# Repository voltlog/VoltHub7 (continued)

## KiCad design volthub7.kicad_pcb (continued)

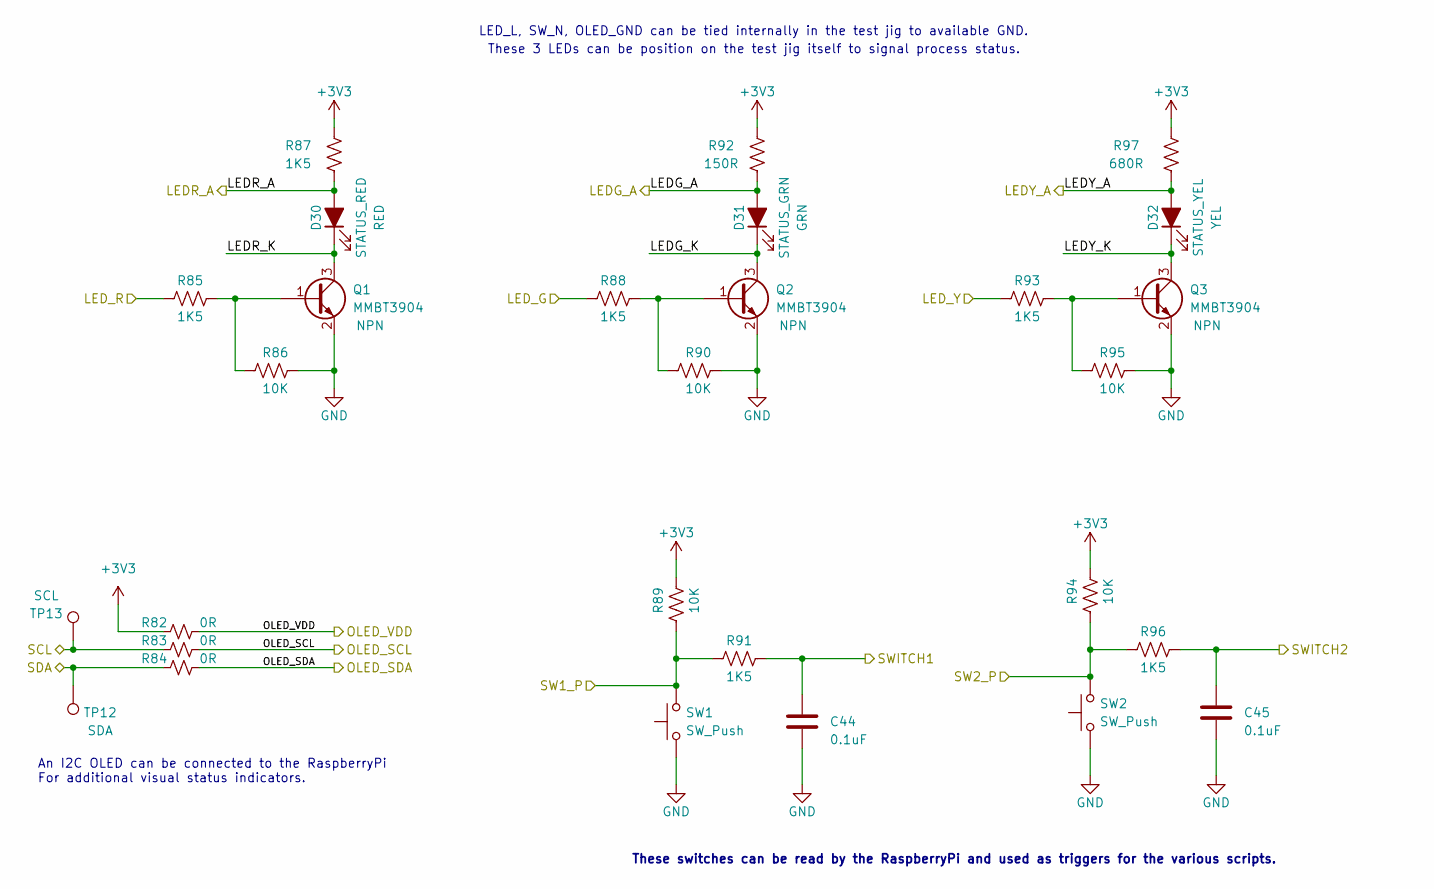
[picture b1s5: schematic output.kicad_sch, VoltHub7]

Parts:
C44, C45: 0.1uF; C_0603_1608Metric; LCSC C14663
D30: STATUS_RED; LED_0603_1608Metric; LCSC C193902
D31: STATUS_GRN; LED_0603_1608Metric; LCSC C84267
D32: STATUS_YEL; LED_0603_1608Metric; LCSC C84268
Q1, Q2, Q3: MMBT3904; SOT-23; LCSC C20526
R82, R83, R84: 0R; R_0603_1608Metric; LCSC C21189
R85, R87, R88, R91, R93, R96: 1K5; R_0603_1608Metric; LCSC C21190
R86, R89, R90, R94, R95: 10K; R_0603_1608Metric; LCSC C25804
R92: 150R; R_0603_1608Metric; LCSC C22808
R97: 680R; R_0603_1608Metric; LCSC C23228
SW1, SW2: SW_Push; SW_SPST_Omron_B3FS-100xP
TP12: SDA; TestPoint_Pad_D1.0mm
TP13: SCL; TestPoint_Pad_D1.0mm

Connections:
+3V3: R82.1, R87.1, R89.1, R92.2, R94.1, R97.2; also elsewhere on the board
/GPIO18: C45.1, R96.1; also elsewhere on the board
/LEDG_A: D31.2 (A), R92.1; also elsewhere on the board
/LEDR_A: D30.2 (A), R87.2; also elsewhere on the board
/Output/LEDG_K: D31.1 (K), Q2.3 (C)
/Output/LEDR_K: D30.1 (K), Q1.3 (C)
/Output/LEDY_A: D32.2 (A), R97.1; also elsewhere on the board
/Output/LEDY_K: D32.1 (K), Q3.3 (C)
/Output/LED_G: R88.2; also elsewhere on the board
/Output/LED_R: R85.2; also elsewhere on the board
/Output/LED_Y: R93.2; also elsewhere on the board
/Output/OLED_SCL: R83.2; also elsewhere on the board
/Output/OLED_SDA: R84.2; also elsewhere on the board
/Output/OLED_VDD: R82.2; also elsewhere on the board
/Output/SW1_P: R89.2, R91.2, SW1.2; also elsewhere on the board
/Output/SW2_P: R94.2, R96.2, SW2.2; also elsewhere on the board
/Output/SWITCH1: C44.1, R91.1; also elsewhere on the board
/SCL/CFG_SEL0: R83.1, TP13.1; also elsewhere on the board
/SDA: R84.1, TP12.1; also elsewhere on the board
GND: C44.2, C45.2, Q1.2 (E), Q2.2 (E), Q3.2 (E), R86.1, R90.1, R95.1, SW1.1, SW2.1; also elsewhere on the board
unnamed: Q1.1 (B), R85.1, R86.2
unnamed: Q2.1 (B), R88.1, R90.2
unnamed: Q3.1 (B), R93.1, R95.2

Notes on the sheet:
These switches can be read by the RaspberryPi and used as triggers for the various scripts.
LED_L, SW_N, OLED_GND can be tied internally in the test jig to available GND.
An I2C OLED can be connected to the RaspberryPi For additional visual status indicators.
These 3 LEDs can be position on the test jig itself to signal process status.

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
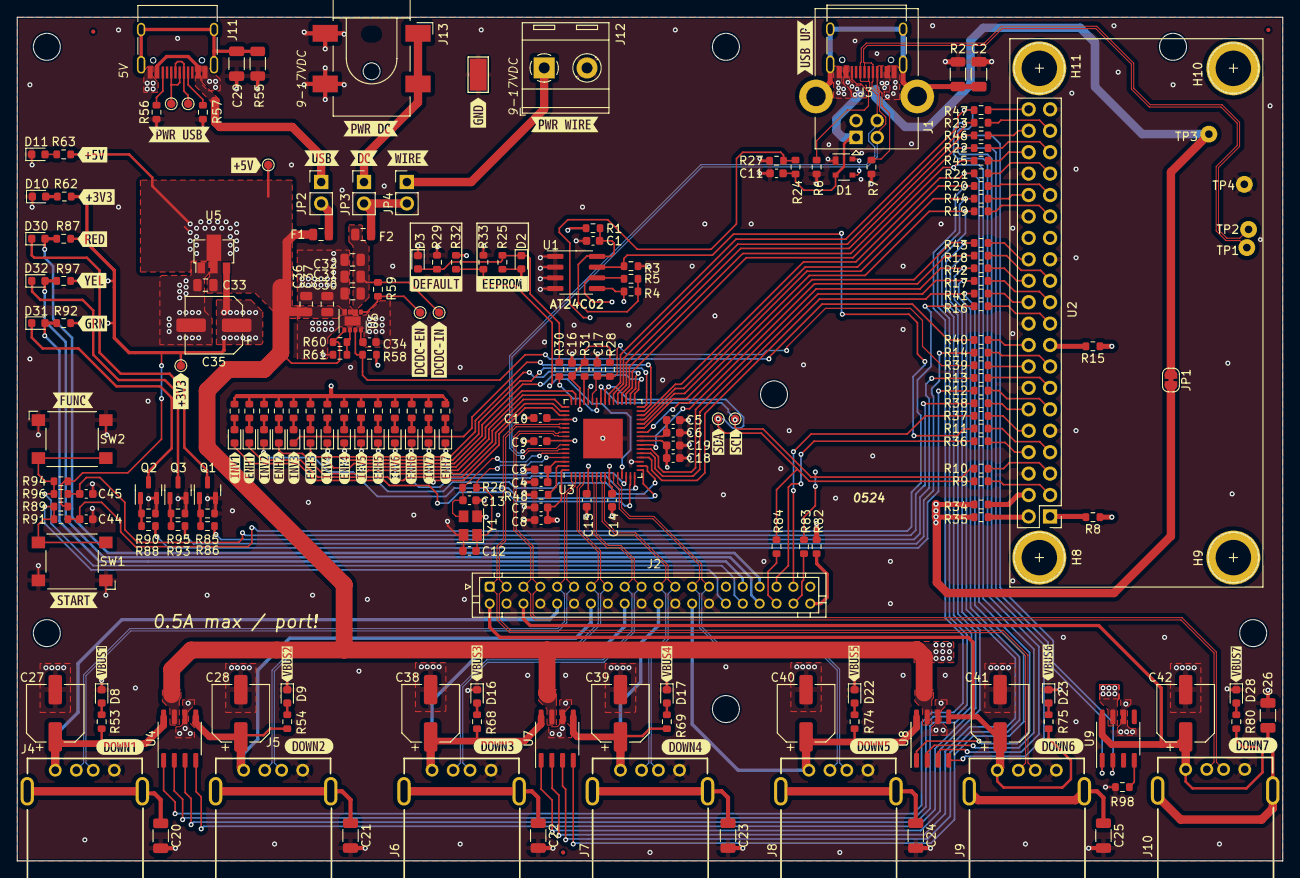
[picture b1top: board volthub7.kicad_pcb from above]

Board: 4 copper layers, 150.0 x 100.0 mm, 281 parts (0 on the bottom side), 168 nets.

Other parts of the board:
C2: 4.7nF; C_1206_3216Metric
kibuzzard-65BCE967: G***; kibuzzard-65BCE967
kibuzzard-65BCEA26: G***; kibuzzard-65BCEA26
kibuzzard-65BCEB9B: G***; kibuzzard-65BCEB9B
kibuzzard-65BCEB17: G***; kibuzzard-65BCEB17
kibuzzard-65BCEB28: G***; kibuzzard-65BCEB28
kibuzzard-65BCEB39: G***; kibuzzard-65BCEB39
kibuzzard-65BCEB78: G***; kibuzzard-65BCEB78
kibuzzard-65BCEB84: G***; kibuzzard-65BCEB84
kibuzzard-65BCEBAB: G***; kibuzzard-65BCEBAB
kibuzzard-65BCEBCC: G***; kibuzzard-65BCEBCC
kibuzzard-65BCEBF9: G***; kibuzzard-65BCEBF9
kibuzzard-65BCEC24: G***; kibuzzard-65BCEC24
kibuzzard-65BCEC45: G***; kibuzzard-65BCEC45
kibuzzard-65BCEC76: G***; kibuzzard-65BCEC76
kibuzzard-65BCECFE: G***; kibuzzard-65BCECFE
kibuzzard-65BCED0C: G***; kibuzzard-65BCED0C
kibuzzard-65BCED07: G***; kibuzzard-65BCED07
kibuzzard-65BCED15: G***; kibuzzard-65BCED15
kibuzzard-65BCED99: G***; kibuzzard-65BCED99
kibuzzard-65BCEDAD: G***; kibuzzard-65BCEDAD
kibuzzard-65BCEDE4: G***; kibuzzard-65BCEDE4
kibuzzard-65BCEF9B: G***; kibuzzard-65BCEF9B
kibuzzard-65BCEF96: G***; kibuzzard-65BCEF96
kibuzzard-65BCEFA3: G***; kibuzzard-65BCEFA3
kibuzzard-65BCEFA7: G***; kibuzzard-65BCEFA7
kibuzzard-65BCEFAC: G***; kibuzzard-65BCEFAC
kibuzzard-65BCEFB2: G***; kibuzzard-65BCEFB2
kibuzzard-65BCEFB9: G***; kibuzzard-65BCEFB9
kibuzzard-65BCEFD7: G***; kibuzzard-65BCEFD7
kibuzzard-65BCEFE1: G***; kibuzzard-65BCEFE1
kibuzzard-65BCEFE6: G***; kibuzzard-65BCEFE6
kibuzzard-65BCEFEA: G***; kibuzzard-65BCEFEA
kibuzzard-65BCEFEF: G***; kibuzzard-65BCEFEF
kibuzzard-65BCEFF4: G***; kibuzzard-65BCEFF4
kibuzzard-65BCEFF8: G***; kibuzzard-65BCEFF8
kibuzzard-65BCF0AF: G***; kibuzzard-65BCF0AF
kibuzzard-65BCF2C7: G***; kibuzzard-65BCF2C7
kibuzzard-65BCF2D0: G***; kibuzzard-65BCF2D0
kibuzzard-65BCF08A: G***; kibuzzard-65BCF08A
kibuzzard-65BCF09D: G***; kibuzzard-65BCF09D
kibuzzard-65BCF34D: G***; kibuzzard-65BCF34D
kibuzzard-65BCF35A: G***; kibuzzard-65BCF35A
kibuzzard-65BCF37C: G***; kibuzzard-65BCF37C
kibuzzard-65BCF060: G***; kibuzzard-65BCF060
kibuzzard-65BCF085: G***; kibuzzard-65BCF085
kibuzzard-65BCF092: G***; kibuzzard-65BCF092
kibuzzard-65BCF099: G***; kibuzzard-65BCF099
kibuzzard-65BCF323: G***; kibuzzard-65BCF323
kibuzzard-65BCF353: G***; kibuzzard-65BCF353
kibuzzard-65BCF360: G***; kibuzzard-65BCF360
kibuzzard-65BCF377: G***; kibuzzard-65BCF377

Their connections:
GND: C2.2; also elsewhere on the board

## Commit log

2024-01-26 started schematic capture
2024-02-27 public release revA
